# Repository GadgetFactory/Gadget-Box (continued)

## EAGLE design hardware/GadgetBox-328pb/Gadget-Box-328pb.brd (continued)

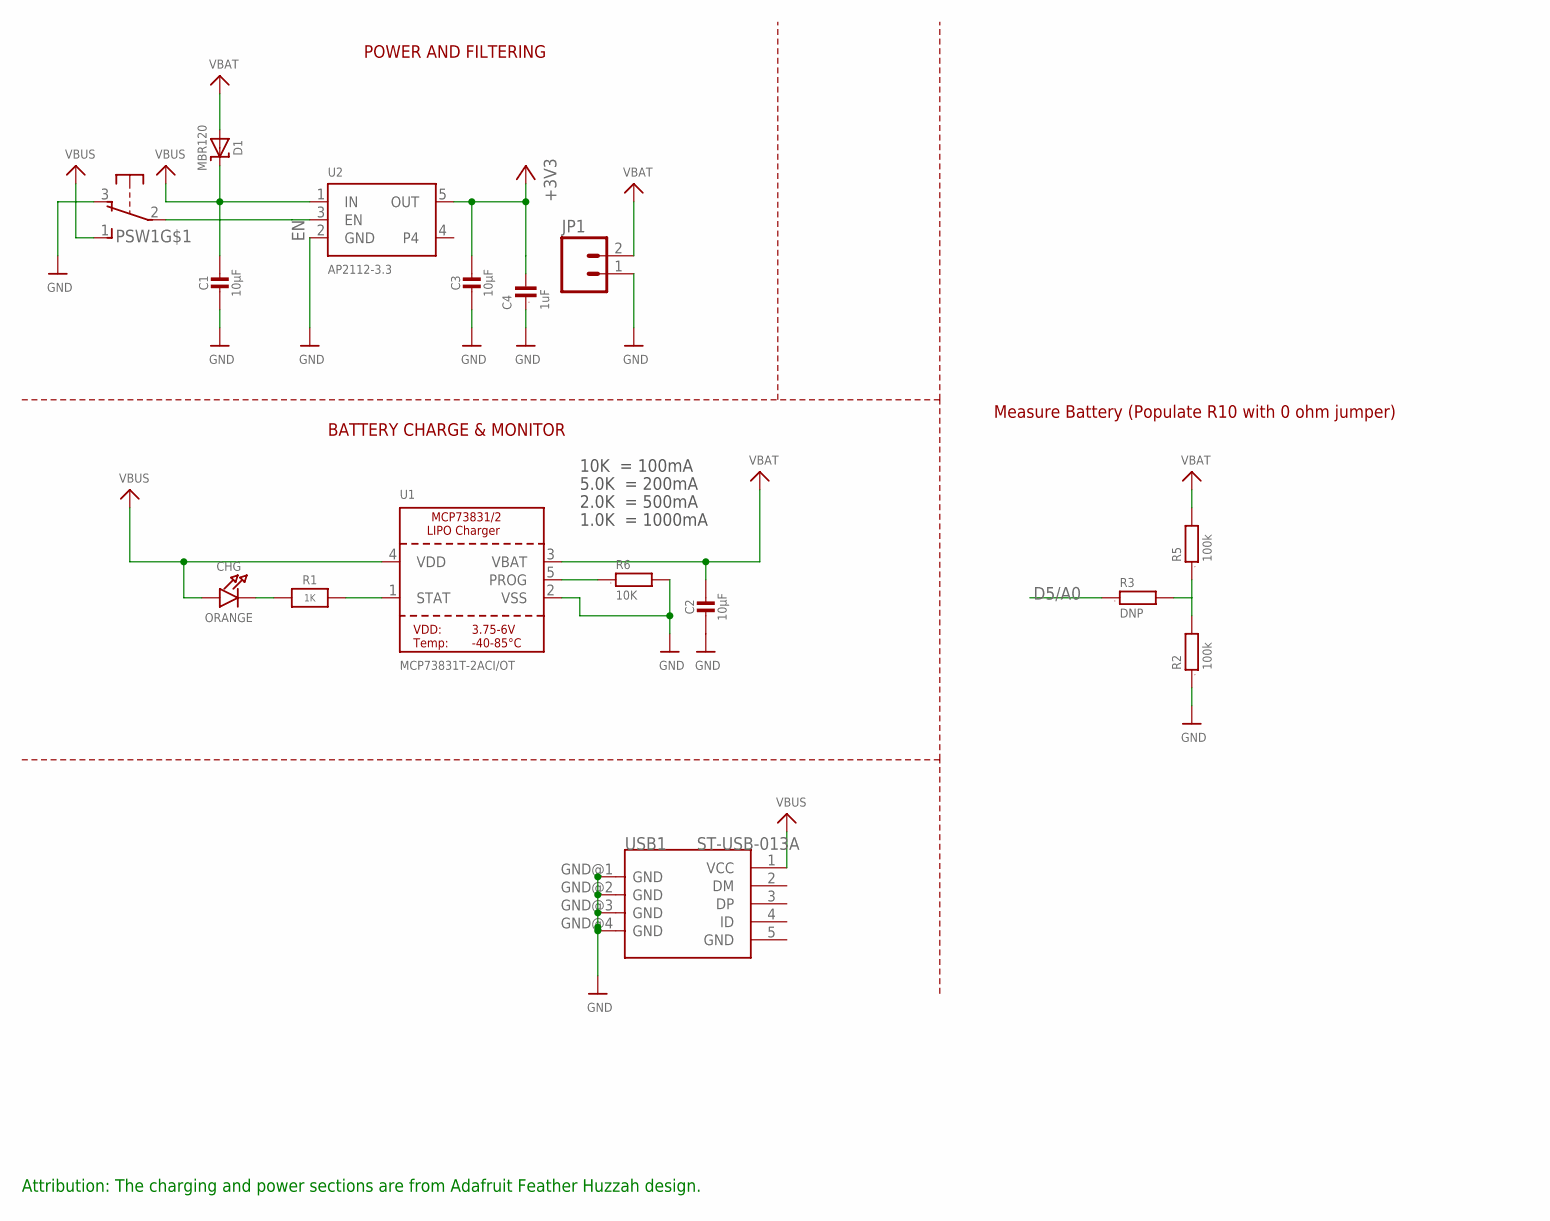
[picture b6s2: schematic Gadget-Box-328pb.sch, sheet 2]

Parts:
C1, C2, C3: 10µF; 0805-NO; PARTNO CL21F106ZPFNNNE,Samsung,DK,1276-3012-1-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
C4: 1uF; 0603; PARTNO C1608X5R1A105K080AC,TDK CORPORATION (VA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
CHG: ORANGE; CHIPLED_0805_NOOUTLINE; PARTNO LTST-C171EKT,LITE-ON INC (VA),DK,160-14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
D1: MBR120; SOD-123; PARTNO MBR120VLSFT3G,on semiconductor,dk,MBR12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
JP1: M02-JST-2-PTH-NO_SILK; JST-2-PTH-NS; PARTNO B2B-PH-SM4-TB(LF)(SN),JST SALES AMERICA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
PSW1: OS102011MA1Q; PARTNO OS102011MA1QN1,C&K Components,dk,CKN955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
R1: 1K; 0603-NO; PARTNO RC0603JR-071KL,YAGEO (VA),dk,311-1.0KGR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
R2, R5: 100k; 0603; PARTNO RC0603JR-07100KL,YAGEO (VA),dk,311-100K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
R3: DNP; 0603
R6: 10K; 0603; PARTNO RC0603JR-0710KL,YAGEO (VA),dk,311-10KGR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
U1: MCP73831T-2ACI/OT; SOT23-5; PARTNO MCP73831T-2ACI/OT,MICROCHIP TECHNOLOGY 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
U2: AP2112-3.3; SOT23-5; PARTNO AP2112K-3.3TRG1,Diodes Incorporated,dk,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
USB1: ST-USB-013A; MINIUSB5+4P-0.8-90D

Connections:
3V3: C3.1, C4.2, U2.5 (OUT); also elsewhere on the board
5V0: C1.1, CHG.A, D1.C, PSW1.1 (S), U1.4 (VDD), U2.1 (IN); also elsewhere on the board
D5/A0: R3.1; also elsewhere on the board
EN: PSW1.2, U2.3 (EN)
GND: C1.2, C2.2, C3.2, C4.1, JP1.1, PSW1.3 (O), R2.1, R6.2, U1.2 (VSS), U2.2 (GND), USB1.GND@1 (GND), USB1.GND@2 (GND), USB1.GND@3 (GND), USB1.GND@4 (GND); also elsewhere on the board
unnamed: CHG.C, R1.1
unnamed: R2.2, R3.2, R5.1
unnamed: R1.2, U1.1 (STAT)
unnamed: R6.1, U1.5 (PROG)
VBAT: C2.1, D1.A, JP1.2, R5.2, U1.3 (VBAT)
VBUS: USB1.1 (VCC)

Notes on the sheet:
POWER AND FILTERING
10K = 100mA
5.0K = 200mA
2.0K = 500mA
1.0K = 1000mA
BATTERY CHARGE & MONITOR
Measure Battery (Populate R10 with 0 ohm jumper)
Attribution: The charging and power sections are from Adafruit Feather Huzzah design.

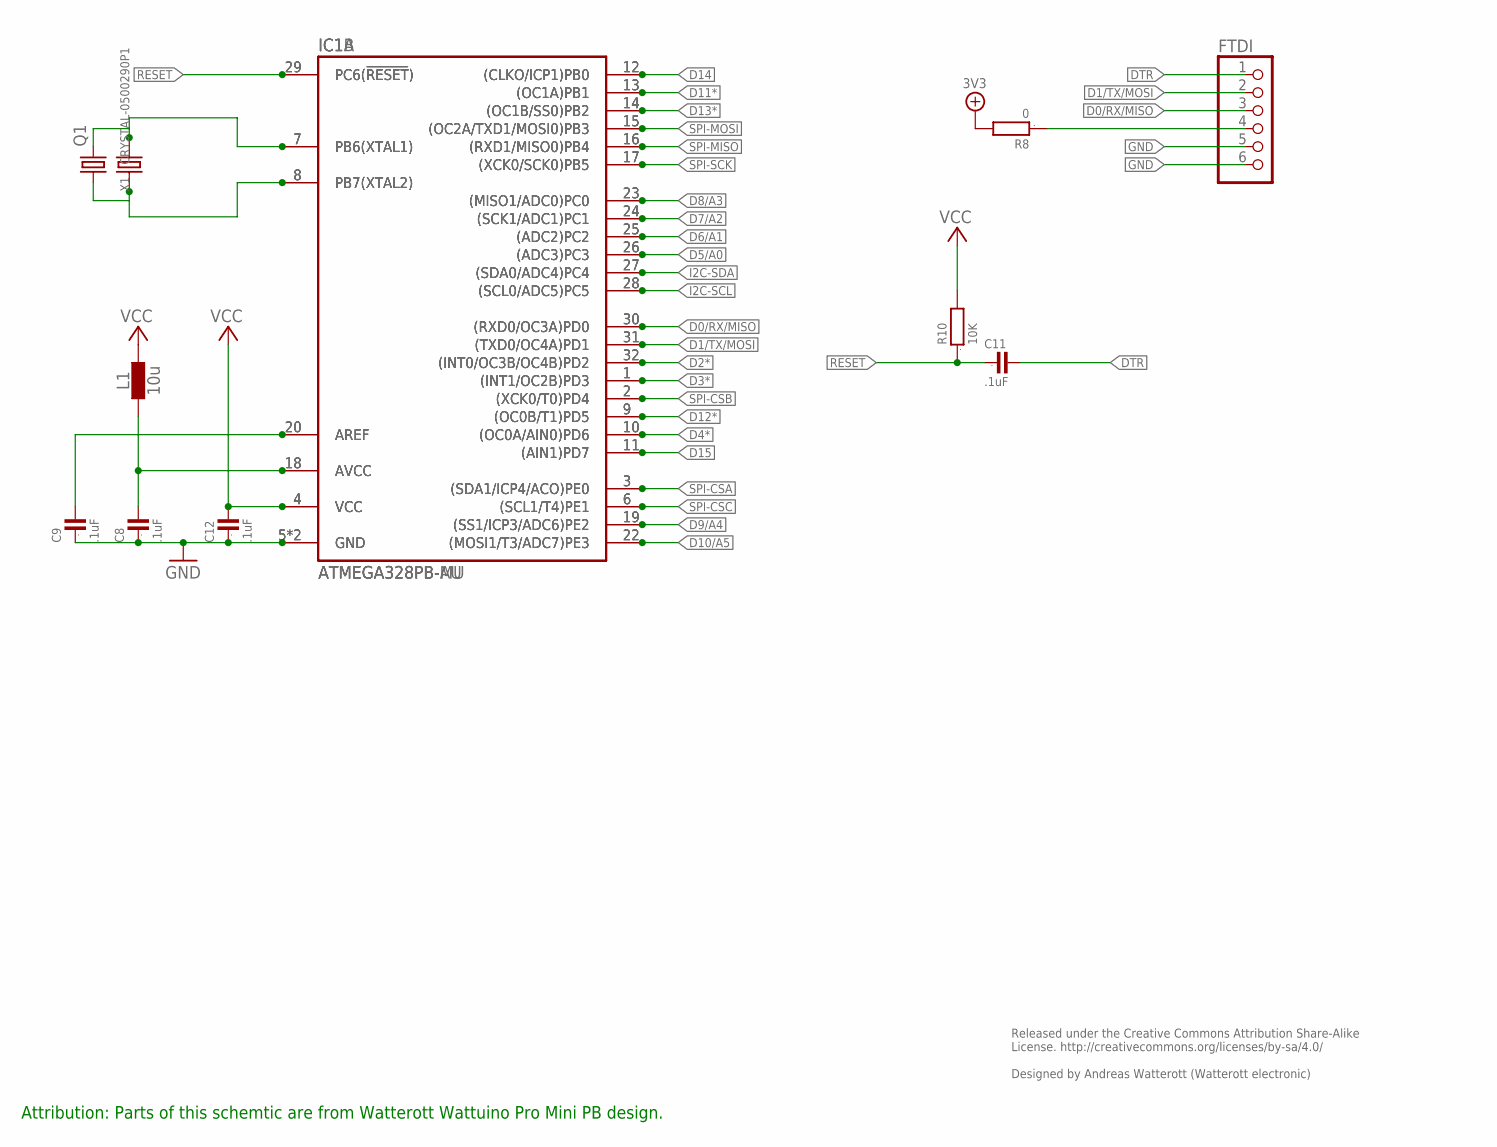
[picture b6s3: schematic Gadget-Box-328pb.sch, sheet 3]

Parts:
C8, C9, C11, C12: .1uF; 0805; PARTNO GRM21BR71E104KA01L,MURATA ELECTRONICS (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
FTDI: PINHD-1X6; 1X06; PARTNO PPPC061LGBN-RC,SULLINS CONNECTOR SOLUTI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
IC1A: ATMEGA328PB-AU; TQFP32; PARTNO ATMEGA328PB-AUR,ATMEL (VA),dk,ATMEGA328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
IC1B: ATMEGA328PB-MU; QFN32-PAD
L1: 10u; C0603; PARTNO MLZ1608E100M,TDK CORPORATION (VA),dk,44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
Q1: CRYSTALSM49; SM49; PARTNO ABLS-8.000MHZ-B4-T,Abracon Corporation,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
R8: 0; 0603
R10: 10K; 0603; PARTNO RC0603JR-0710KL,YAGEO (VA),dk,311-10KGR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
X1: CRYSTAL-0500290P1; 2P-SMD-5.0X3.2; PARTNO ABM3-8.000MHZ-D2Y-T,Abracon Corporation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

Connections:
3V3: C12.2, IC1A.4 (VCC), IC1B.4 (VCC), L1.2, R8.2, R10.2; also elsewhere on the board
AREF: C9.2, IC1A.20 (AREF), IC1B.20 (AREF)
AVCC: C8.2, IC1A.18 (AVCC), IC1B.18 (AVCC), L1.1
D0/RX/MISO: FTDI.3, IC1A.30 ((RXD0/OC3A)PD0), IC1B.30 ((RXD0/OC3A)PD0); also elsewhere on the board
D1/TX/MOSI: FTDI.2, IC1A.31 ((TXD0/OC4A)PD1), IC1B.31 ((TXD0/OC4A)PD1); also elsewhere on the board
D2*: IC1A.32 ((INT0/OC3B/OC4B)PD2), IC1B.32 ((INT0/OC3B/OC4B)PD2); also elsewhere on the board
D3*: IC1A.1 ((INT1/OC2B)PD3), IC1B.1 ((INT1/OC2B)PD3); also elsewhere on the board
D4*: IC1A.10 ((OC0A/AIN0)PD6), IC1B.10 ((OC0A/AIN0)PD6); also elsewhere on the board
D5/A0: IC1A.26 ((ADC3)PC3), IC1B.26 ((ADC3)PC3); also elsewhere on the board
D6/A1: IC1A.25 ((ADC2)PC2), IC1B.25 ((ADC2)PC2); also elsewhere on the board
D7/A2: IC1A.24 ((SCK1/ADC1)PC1), IC1B.24 ((SCK1/ADC1)PC1); also elsewhere on the board
D8/A3: IC1A.23 ((MISO1/ADC0)PC0), IC1B.23 ((MISO1/ADC0)PC0); also elsewhere on the board
D9/A4: IC1A.19 ((SS1/ICP3/ADC6)PE2), IC1B.19 ((SS1/ICP3/ADC6)PE2); also elsewhere on the board
D10/A5: IC1A.22 ((MOSI1/T3/ADC7)PE3), IC1B.22 ((MOSI1/T3/ADC7)PE3); also elsewhere on the board
D11*: IC1A.13 ((OC1A)PB1), IC1B.13 ((OC1A)PB1); also elsewhere on the board
D12*: IC1A.9 ((OC0B/T1)PD5), IC1B.9 ((OC0B/T1)PD5); also elsewhere on the board
D13*: IC1A.14 ((OC1B/SS0)PB2), IC1B.14 ((OC1B/SS0)PB2); also elsewhere on the board
D14: IC1A.12 ((CLKO/ICP1)PB0), IC1B.12 ((CLKO/ICP1)PB0); also elsewhere on the board
D15: IC1A.11 ((AIN1)PD7), IC1B.11 ((AIN1)PD7); also elsewhere on the board
DTR: C11.2, FTDI.1
GND: C8.1, C9.1, C12.1, FTDI.5, FTDI.6, IC1A.5 (GND), IC1A.21 (GND), IC1B.5 (GND), IC1B.21 (GND); also elsewhere on the board
I2C-SCL: IC1A.28 ((SCL0/ADC5)PC5), IC1B.28 ((SCL0/ADC5)PC5); also elsewhere on the board
I2C-SDA: IC1A.27 ((SDA0/ADC4)PC4), IC1B.27 ((SDA0/ADC4)PC4); also elsewhere on the board
unnamed: IC1A.8 (PB7(XTAL2)), IC1B.8 (PB7(XTAL2)), Q1.1, X1.1
unnamed: IC1A.7 (PB6(XTAL1)), IC1B.7 (PB6(XTAL1)), Q1.2, X1.2
unnamed: FTDI.4, R8.1
RESET: C11.1, IC1A.29 (PC6(!RESET!)), IC1B.29 (PC6(!RESET!)), R10.1; also elsewhere on the board
SPI-CSA: IC1A.3 ((SDA1/ICP4/ACO)PE0), IC1B.3 ((SDA1/ICP4/ACO)PE0); also elsewhere on the board
SPI-CSB: IC1A.2 ((XCK0/T0)PD4), IC1B.2 ((XCK0/T0)PD4); also elsewhere on the board
SPI-CSC: IC1A.6 ((SCL1/T4)PE1), IC1B.6 ((SCL1/T4)PE1); also elsewhere on the board
SPI-MISO: IC1A.16 ((RXD1/MISO0)PB4), IC1B.16 ((RXD1/MISO0)PB4); also elsewhere on the board
SPI-MOSI: IC1A.15 ((OC2A/TXD1/MOSI0)PB3), IC1B.15 ((OC2A/TXD1/MOSI0)PB3); also elsewhere on the board
SPI-SCK: IC1A.17 ((XCK0/SCK0)PB5), IC1B.17 ((XCK0/SCK0)PB5); also elsewhere on the board

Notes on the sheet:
Released under the Creative Commons Attribution Share-Alike License. http://creativecommons.org/licenses/by-sa/4.0/ Designed by Andreas Watterott (Watterott electronic)
Attribution: Parts of this schemtic are from Watterott Wattuino Pro Mini PB design.

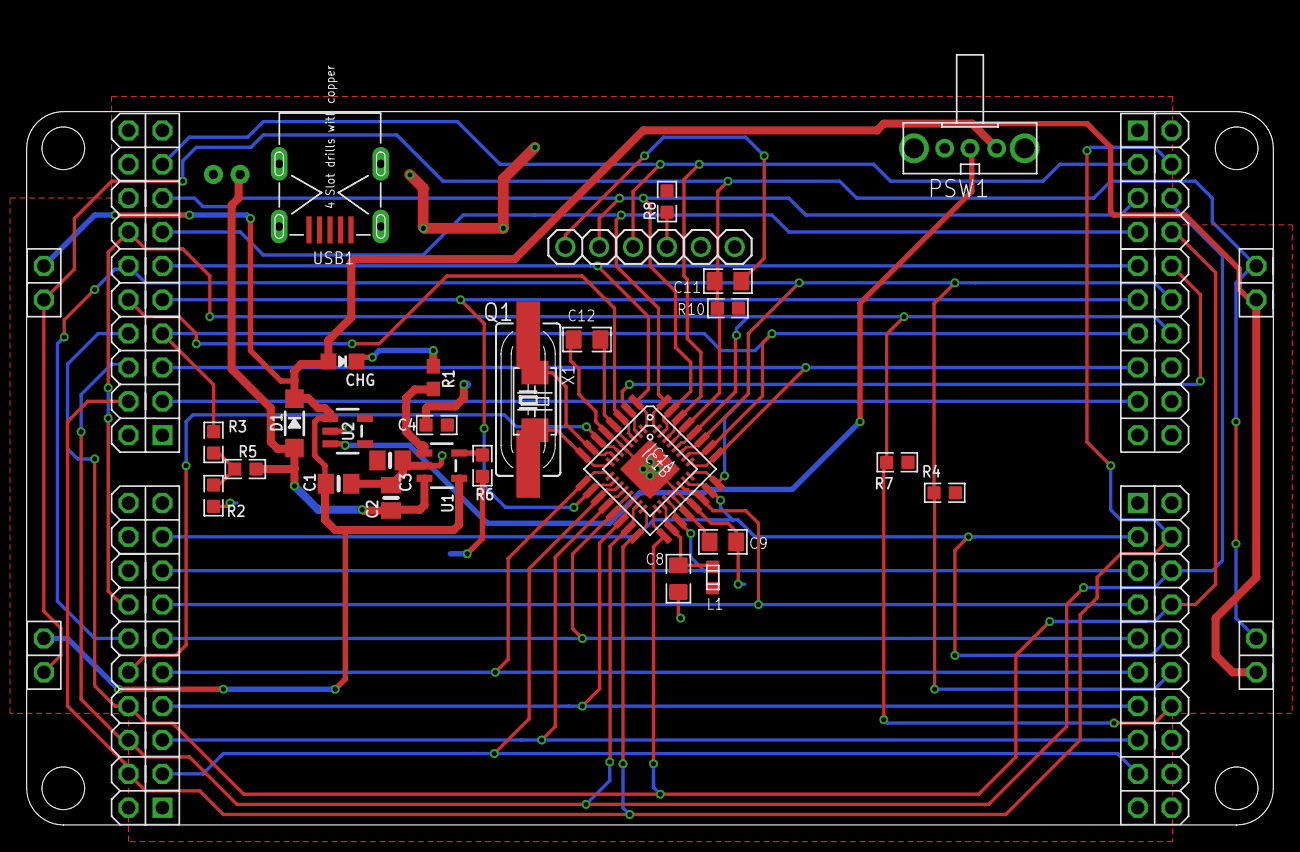
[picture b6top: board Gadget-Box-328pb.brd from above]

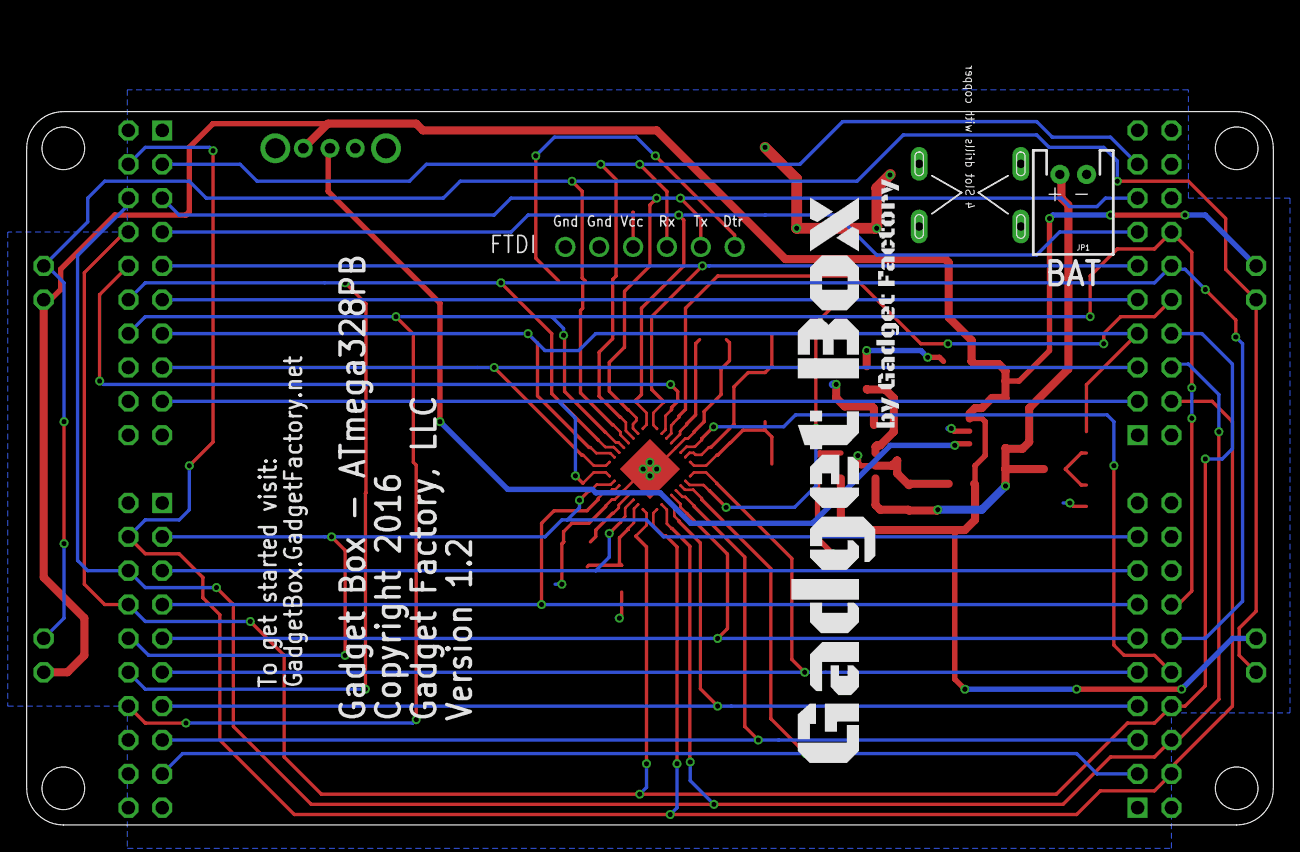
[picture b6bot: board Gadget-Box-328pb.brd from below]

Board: 2 copper layers, 93.4 x 59.7 mm, 36 parts (2 on the bottom side), 40 nets.

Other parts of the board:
$$U$1: ECOG93P53P5
U$100: GADGETBOX_TEXT

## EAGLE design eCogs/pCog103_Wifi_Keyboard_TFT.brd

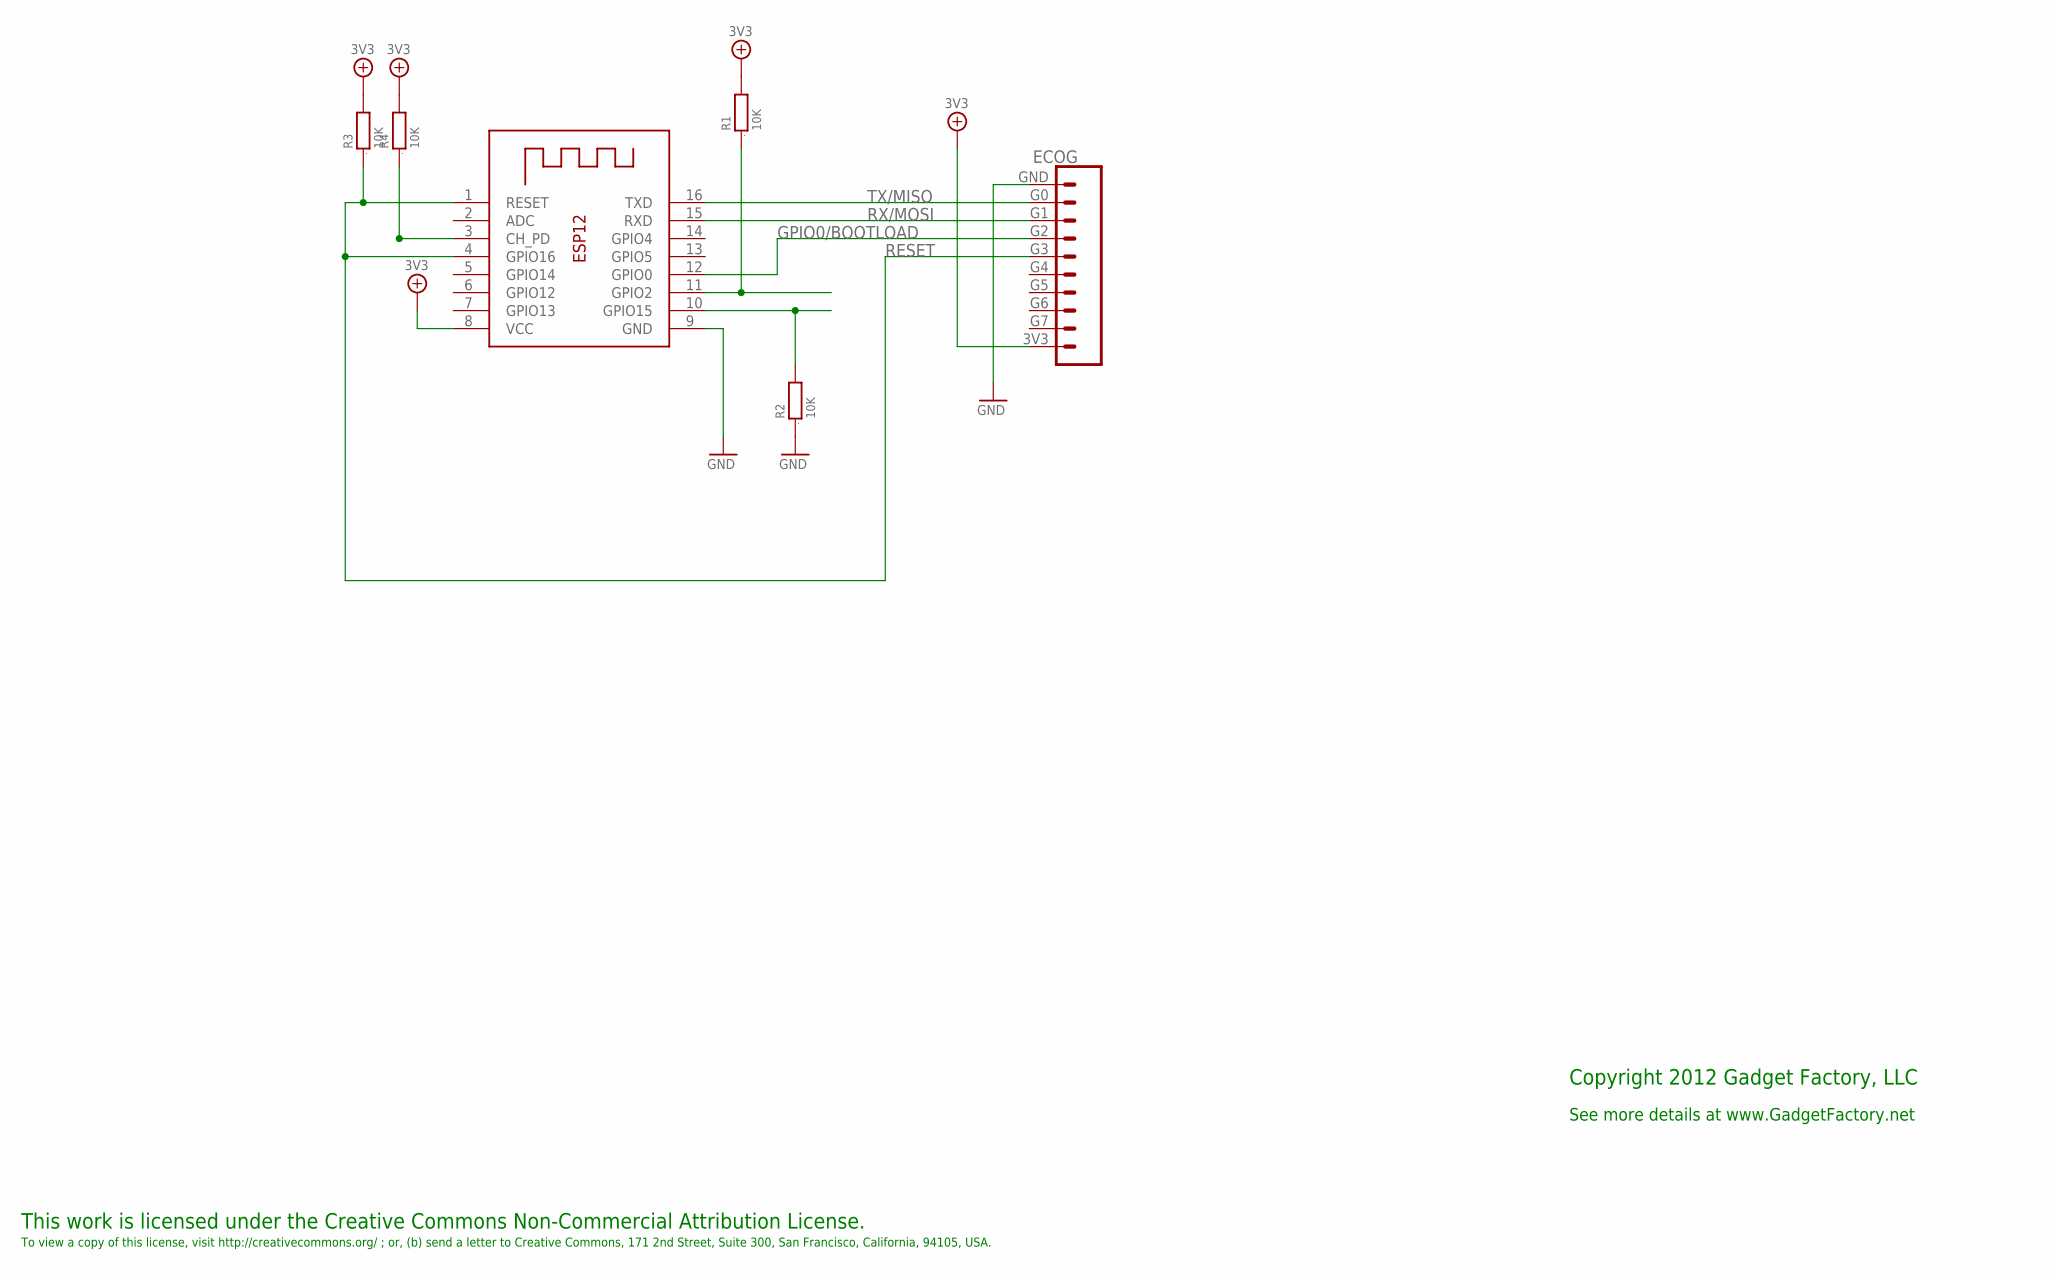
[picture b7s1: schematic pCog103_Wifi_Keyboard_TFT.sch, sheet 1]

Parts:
ECOG: ECOG_GENERAL_ROWTHROUGHOLE; ECOG_GENERAL_TH
R1, R2, R3, R4: 10K; 0805; DIGIKEY RMCF0805JT10K0CT-ND
X1: ESP-12

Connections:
3V3: ECOG.3V3, R1.2, R3.2, R4.2, X1.8 (VCC); also elsewhere on the board
GND: ECOG.GND, R2.1, X1.9 (GND); also elsewhere on the board
GPIO0/BOOTLOAD: ECOG.G2, X1.12 (GPIO0)
unnamed: R1.1, X1.11 (GPIO2)
unnamed: R2.2, X1.10 (GPIO15)
unnamed: R4.1, X1.3 (CH_PD)
RESET: ECOG.G3, R3.1, X1.1 (RESET), X1.4 (GPIO16)
RX/MOSI: ECOG.G1, X1.15 (RXD)
TX/MISO: ECOG.G0, X1.16 (TXD)

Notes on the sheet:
This work is licensed under the Creative Commons Non-Commercial Attribution License.
To view a copy of this license, visit http://creativecommons.org/ ; or, (b) send a letter to Creative Commons, 171 2nd Street, Suite 300, San Francisco, California, 94105, USA.
Copyright 2012 Gadget Factory, LLC
See more details at www.GadgetFactory.net

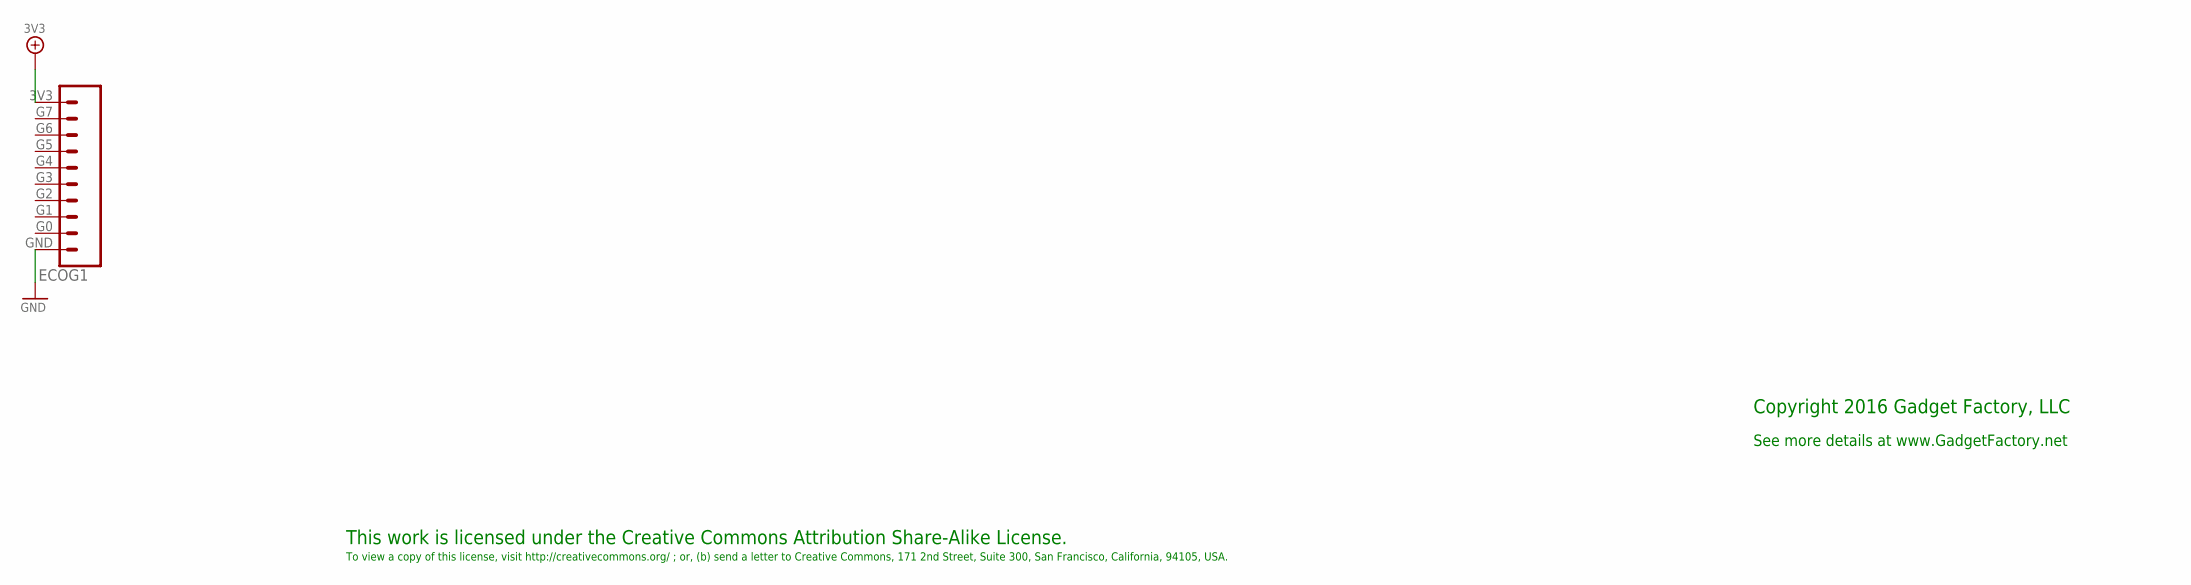
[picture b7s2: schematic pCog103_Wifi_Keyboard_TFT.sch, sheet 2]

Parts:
ECOG1: ECOG_GENERAL_ROWSURFACEMOUNT; ECOG_GENERAL_SMD

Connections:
3V3: ECOG1.3V3; also elsewhere on the board
GND: ECOG1.GND; also elsewhere on the board

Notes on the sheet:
This work is licensed under the Creative Commons Attribution Share-Alike License.
To view a copy of this license, visit http://creativecommons.org/ ; or, (b) send a letter to Creative Commons, 171 2nd Street, Suite 300, San Francisco, California, 94105, USA.
Copyright 2016 Gadget Factory, LLC
See more details at www.GadgetFactory.net

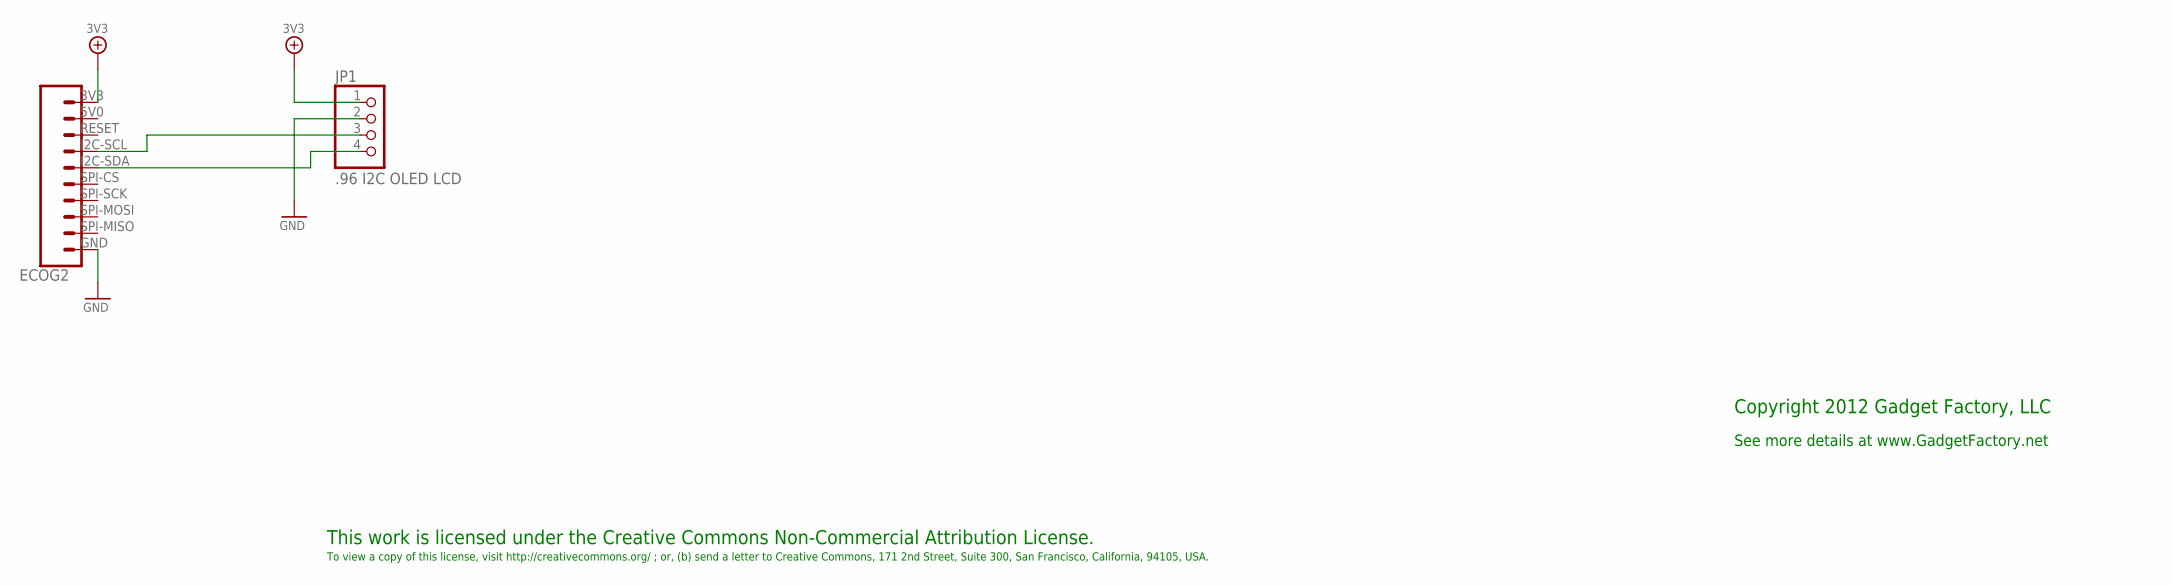
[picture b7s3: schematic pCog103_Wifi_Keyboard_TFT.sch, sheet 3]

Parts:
ECOG2: ECOG_BUSES_ROWTHROUGHHOLE; ECOG_BUSES_TH
JP1: .96 I2C OLED LCD; 1X04

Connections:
3V3: ECOG2.3V3, JP1.1; also elsewhere on the board
GND: ECOG2.GND, JP1.2; also elsewhere on the board
unnamed: ECOG2.I2C-SCL, JP1.3
unnamed: ECOG2.I2C-SDA, JP1.4

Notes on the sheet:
This work is licensed under the Creative Commons Non-Commercial Attribution License.
To view a copy of this license, visit http://creativecommons.org/ ; or, (b) send a letter to Creative Commons, 171 2nd Street, Suite 300, San Francisco, California, 94105, USA.
Copyright 2012 Gadget Factory, LLC
See more details at www.GadgetFactory.net

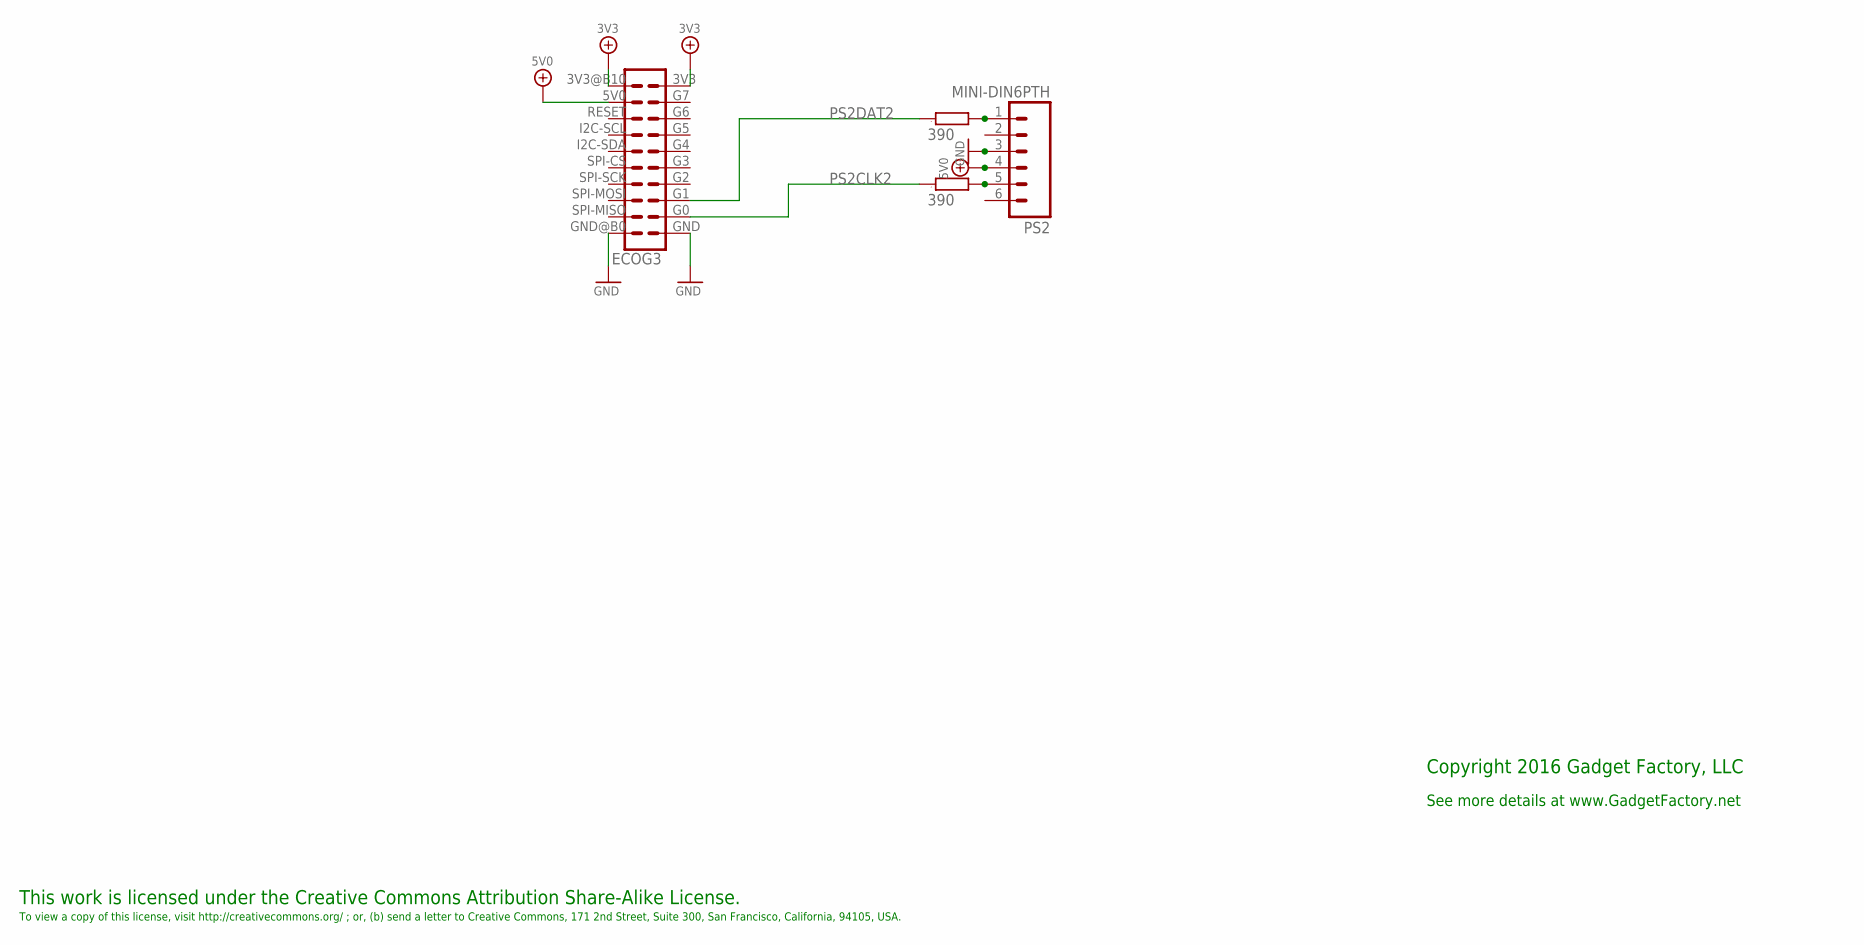
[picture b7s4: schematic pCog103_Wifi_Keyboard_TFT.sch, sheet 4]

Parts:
ECOG3: ECOG_DUALTHROUGHHOLE; ECOG_DUAL_TH
PS2: MINI-DIN6PTH; MINI-DIN6
R5, R6: 390; 0603

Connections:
3V3: ECOG3.3V3, ECOG3.3V3@B10 (3V3); also elsewhere on the board
5V0: ECOG3.5V0 (5V), PS2.4
GND: ECOG3.GND, ECOG3.GND@B0 (GND), PS2.3; also elsewhere on the board
unnamed: PS2.1, R5.2
unnamed: PS2.5, R6.2
PS2CLK2: ECOG3.G0, R6.1
PS2DAT2: ECOG3.G1, R5.1

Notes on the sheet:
This work is licensed under the Creative Commons Attribution Share-Alike License.
To view a copy of this license, visit http://creativecommons.org/ ; or, (b) send a letter to Creative Commons, 171 2nd Street, Suite 300, San Francisco, California, 94105, USA.
Copyright 2016 Gadget Factory, LLC
See more details at www.GadgetFactory.net

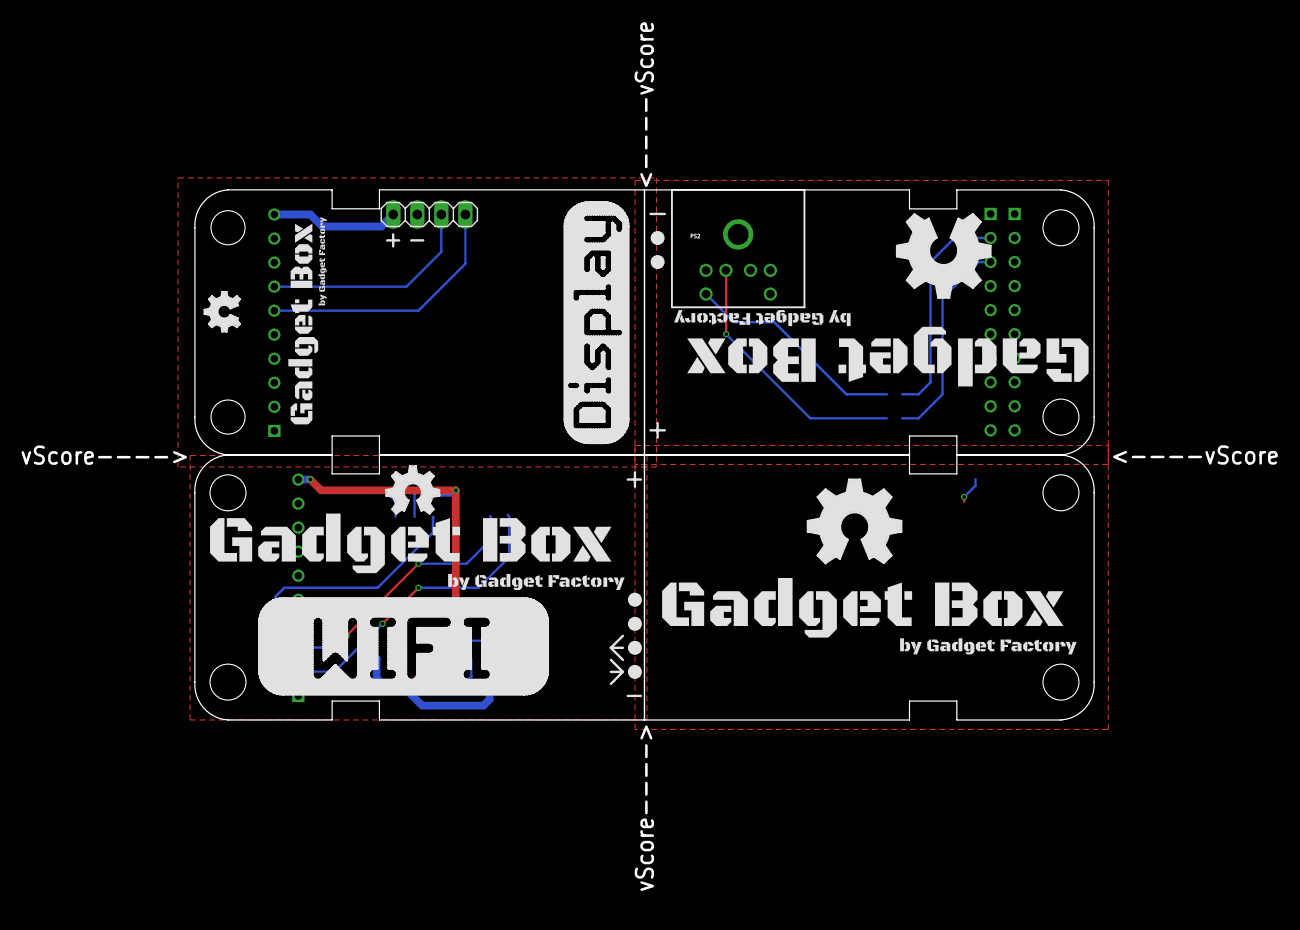
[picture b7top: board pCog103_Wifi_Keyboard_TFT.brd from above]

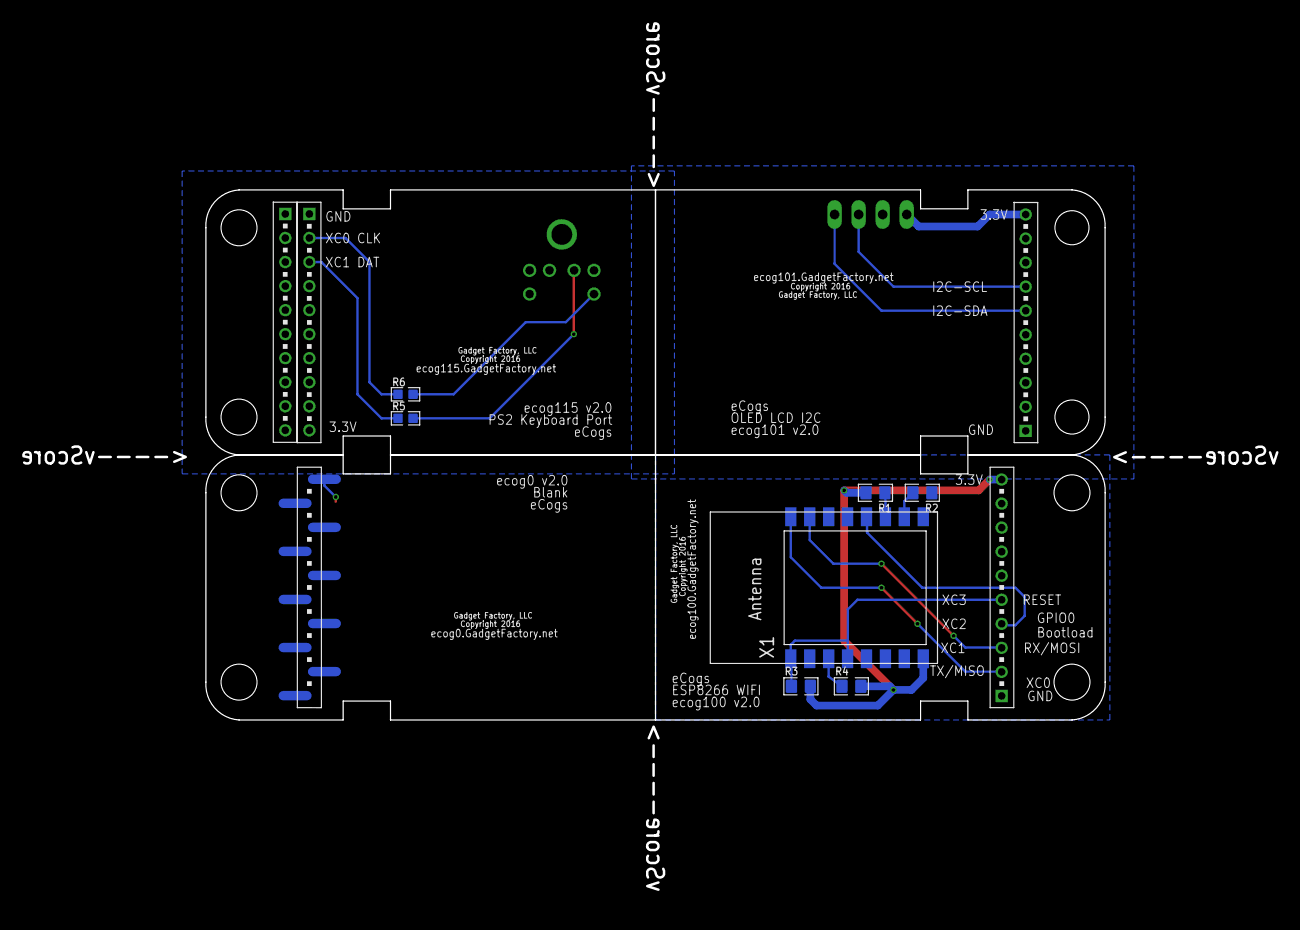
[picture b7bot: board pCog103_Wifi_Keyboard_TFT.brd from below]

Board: 2 copper layers, 133.2 x 94.1 mm, 27 parts (7 on the bottom side), 16 nets.

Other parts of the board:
U$1, U$7, U$12: GADGETBOX_TEXT
U$2, U$3, U$4, U$5, U$11, U$14: LEGEND_DIO
U$6: OSHW_FILLX200_NOTEXT
U$8, U$13: OSHW_FILLX350_NOTEXT
U$9: GADGETBOX_SMALL
U$10: OSHW_FILLX150_NOTEXT
